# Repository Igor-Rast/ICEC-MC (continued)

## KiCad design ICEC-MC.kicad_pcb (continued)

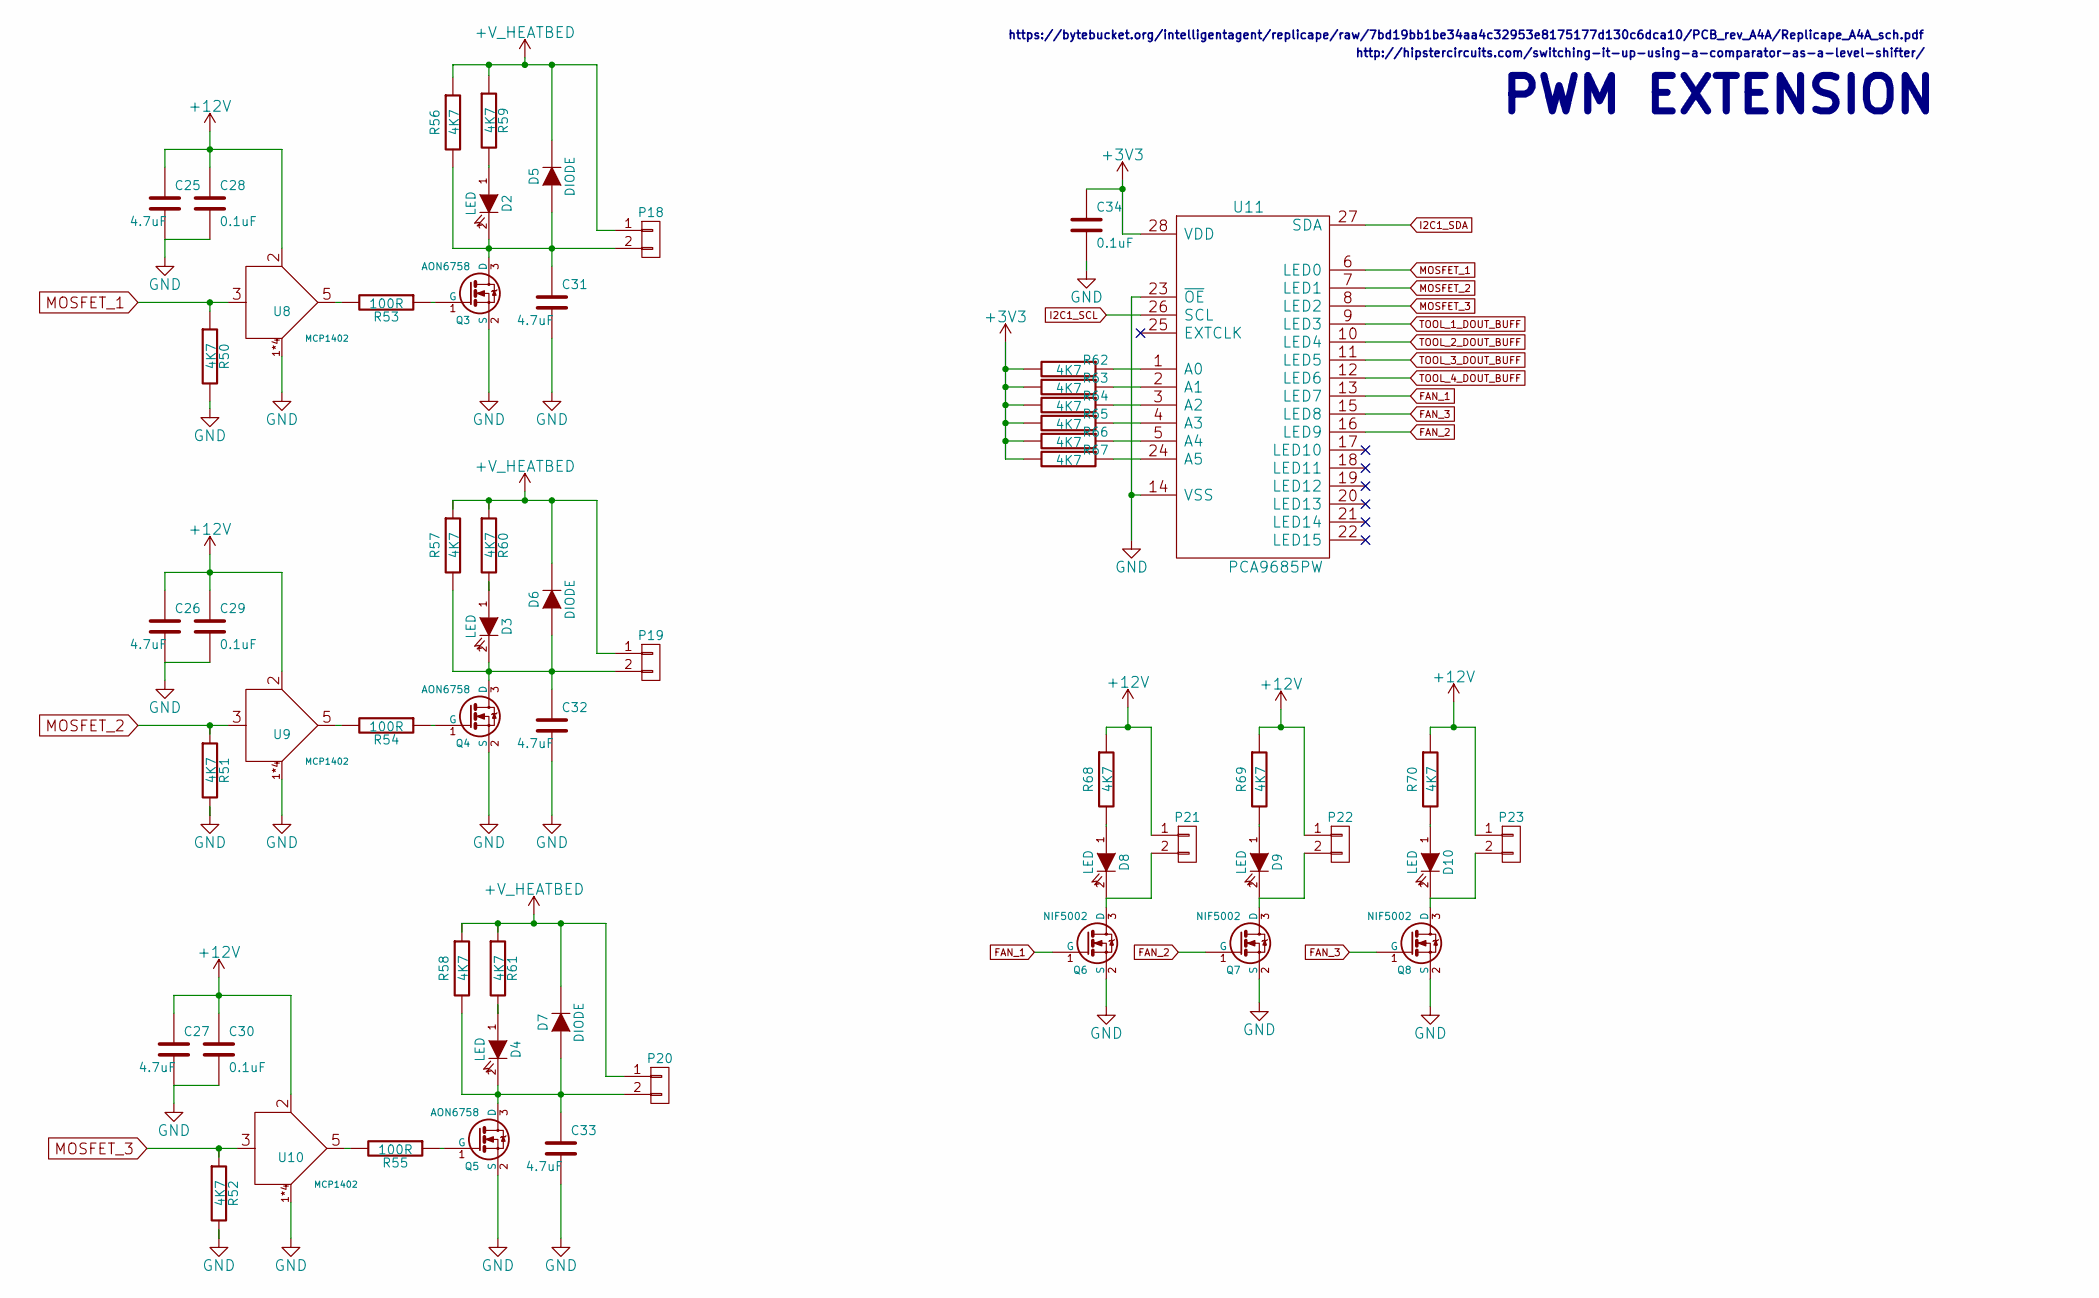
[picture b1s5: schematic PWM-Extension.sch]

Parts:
C25, C26, C27, C31, C32, C33: 4.7uF; C_0805_HandSoldering
C28, C29, C30, C34: 0.1uF; C_0805_HandSoldering
D2, D3, D4, D9, D10: LED; LED-0603
D5, D6, D7: DIODE
D8: LED; LED-0603; DigiKey 475-2816-1-ND
P18, P19, P20, P21, P22, P23: CONN_01X02; Socket_Strip_Straight_1x02
Q3, Q4, Q5: AON6758
Q6, Q7, Q8: NIF5002
R50, R51, R52, R56, R57, R58, R59, R60, R61, R62, R63, R64, R65, R66, R67, R68, R69, R70: 4K7; R_0805_HandSoldering
R53, R54, R55: 100R; R_0805_HandSoldering
U8, U9, U10: MCP1402
U11: PCA9685PW; TSSOP-28_4.4x9.7mm_Pitch0.65mm

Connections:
+3V3: C34.1, R62.2, R63.2, R64.2, R65.2, R66.2, R67.2, U11.28 (VDD); also elsewhere on the board
FAN_1: Q6.1 (G), U11.13 (LED7)
FAN_2: Q7.1 (G), U11.16 (LED9)
FAN_3: Q8.1 (G), U11.15 (LED8)
I2C1_SCL: U11.26 (SCL); also elsewhere on the board
I2C1_SDA: U11.27 (SDA); also elsewhere on the board
MOSFET_1: R50.1, U8.3, U11.6 (LED0)
MOSFET_2: R51.1, U9.3, U11.7 (LED1)
MOSFET_3: R52.1, U10.3, U11.8 (LED2)
unnamed: C31.1, D2.2 (K), D5.1 (A), P18.2, Q3.3 (D), R56.2
unnamed: C32.1, D3.2 (K), D6.1 (A), P19.2, Q4.3 (D), R57.2
unnamed: C33.1, D4.2 (K), D7.1 (A), P20.2, Q5.3 (D), R58.2
unnamed: D2.1 (A), R59.2
unnamed: D3.1 (A), R60.2
unnamed: D4.1 (A), R61.2
unnamed: D8.1 (A), R68.2
unnamed: D8.2 (K), P21.2, Q6.3 (D)
unnamed: D9.1 (A), R69.2
unnamed: D9.2 (K), P22.2, Q7.3 (D)
unnamed: D10.1 (A), R70.2
unnamed: D10.2 (K), P23.2, Q8.3 (D)
unnamed: Q3.1 (G), R53.1
unnamed: Q4.1 (G), R54.1
unnamed: Q5.1 (G), R55.1
unnamed: R53.2, U8.5
unnamed: R54.2, U9.5
unnamed: R55.2, U10.5
unnamed: R62.1, U11.1 (A0)
unnamed: R63.1, U11.2 (A1)
unnamed: R64.1, U11.3 (A2)
unnamed: R65.1, U11.4 (A3)
unnamed: R66.1, U11.5 (A4)
unnamed: R67.1, U11.24 (A5)
TOOL_1_DOUT_BUFF: U11.9 (LED3); also elsewhere on the board
TOOL_2_DOUT_BUFF: U11.10 (LED4); also elsewhere on the board
TOOL_3_DOUT_BUFF: U11.11 (LED5); also elsewhere on the board
TOOL_4_DOUT_BUFF: U11.12 (LED6); also elsewhere on the board

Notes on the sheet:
PWM EXTENSION
http://hipstercircuits.com/switching-it-up-using-a-comparator-as-a-level-shifter/
https://bytebucket.org/intelligentagent/replicape/raw/7bd19bb1be34aa4c32953e8175177d130c6dca10/PCB_rev_A4A/Replicape_A4A_sch.pdf

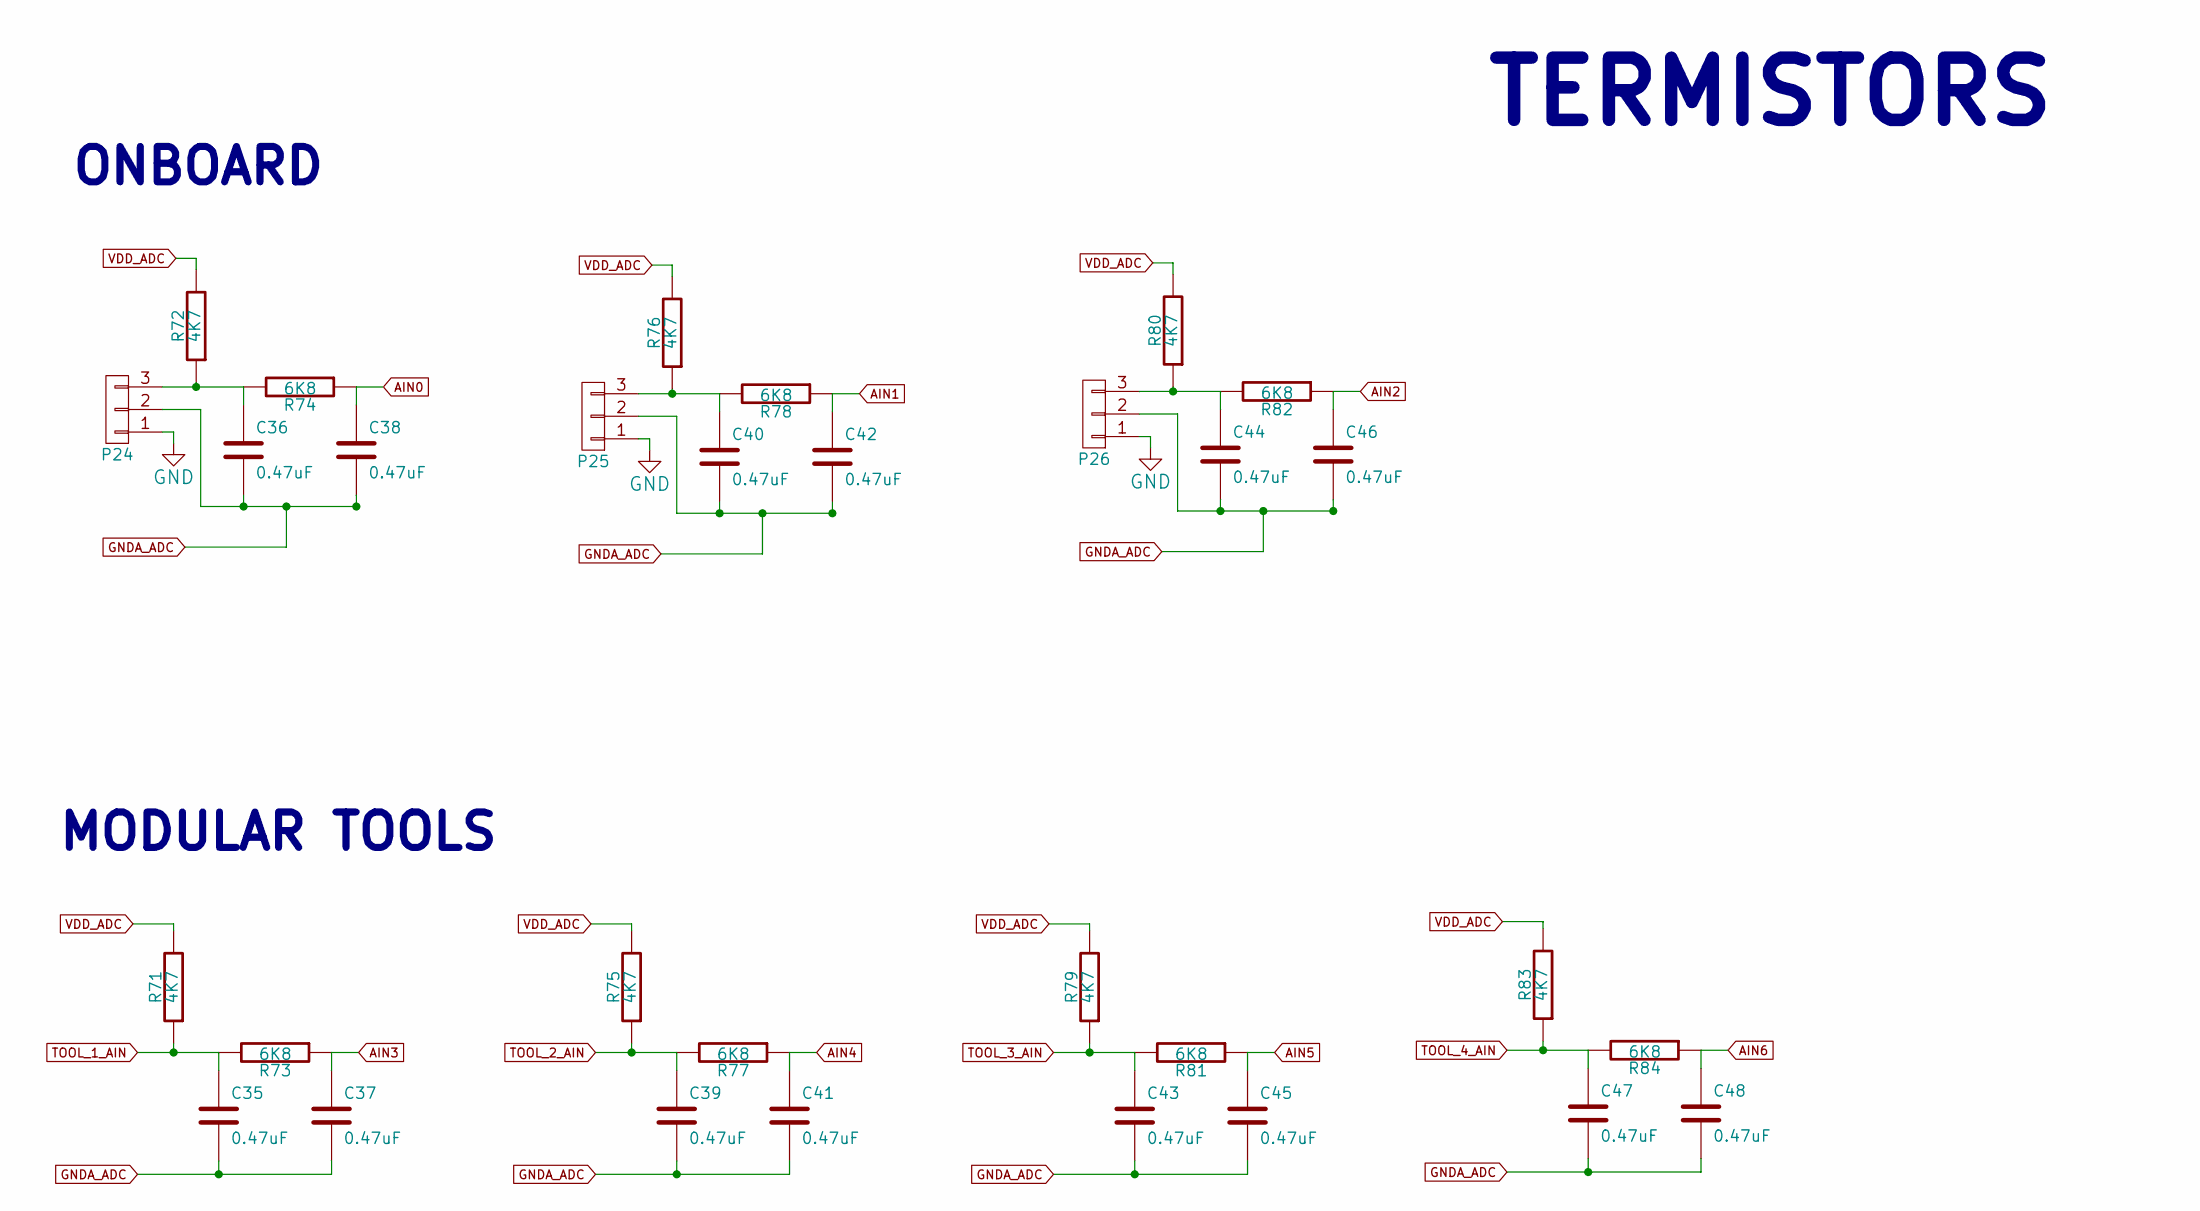
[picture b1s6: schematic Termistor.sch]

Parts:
C35, C36, C37, C38, C39, C40, C41, C42, C43, C44, C45, C46, C47, C48: 0.47uF; C_0805_HandSoldering
P24, P25, P26: CONN_01X03; Socket_Strip_Straight_1x03
R71, R72, R75, R76, R79, R80, R83: 4K7; R_0805_HandSoldering
R73, R74, R77, R78, R81, R82, R84: 6K8; R_0805_HandSoldering

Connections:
AIN0: C38.1, R74.1; also elsewhere on the board
AIN1: C42.1, R78.1; also elsewhere on the board
AIN2: C46.1, R82.1; also elsewhere on the board
AIN3: C37.1, R73.1; also elsewhere on the board
AIN4: C41.1, R77.1; also elsewhere on the board
AIN5: C45.1, R81.1; also elsewhere on the board
AIN6: C48.1, R84.1; also elsewhere on the board
GNDA_ADC: C35.2, C36.2, C37.2, C38.2, C39.2, C40.2, C41.2, C42.2, C43.2, C44.2, C45.2, C46.2, C47.2, C48.2, P24.2, P25.2, P26.2; also elsewhere on the board
unnamed: C36.1, P24.3, R72.1, R74.2
unnamed: C40.1, P25.3, R76.1, R78.2
unnamed: C44.1, P26.3, R80.1, R82.2
TOOL_1_AIN: C35.1, R71.1, R73.2; also elsewhere on the board
TOOL_2_AIN: C39.1, R75.1, R77.2; also elsewhere on the board
TOOL_3_AIN: C43.1, R79.1, R81.2; also elsewhere on the board
TOOL_4_AIN: C47.1, R83.1, R84.2; also elsewhere on the board
VDD_ADC: R71.2, R72.2, R75.2, R76.2, R79.2, R80.2, R83.2; also elsewhere on the board

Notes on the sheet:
TERMISTORS
ONBOARD
MODULAR TOOLS

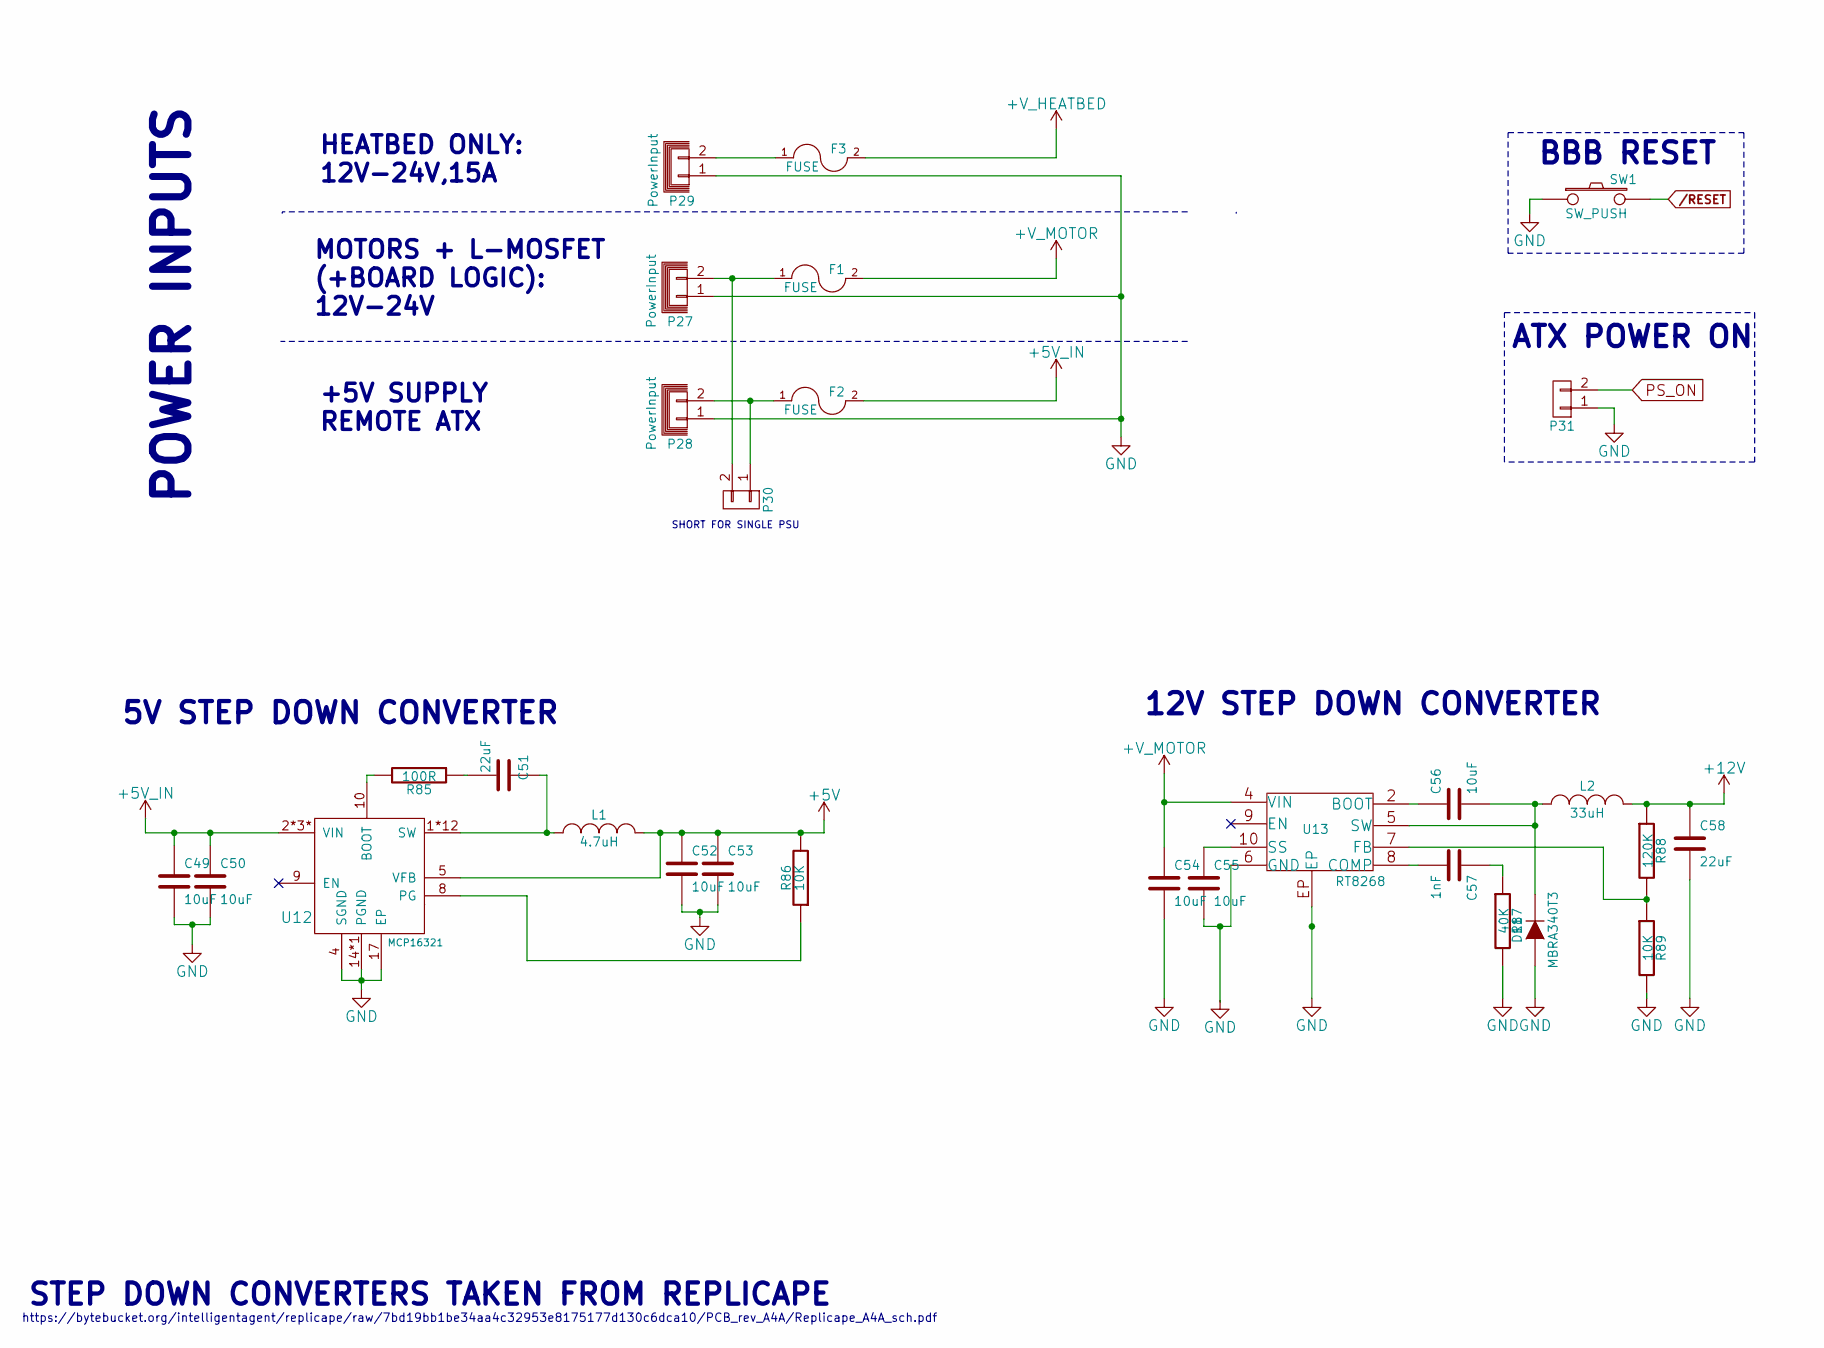
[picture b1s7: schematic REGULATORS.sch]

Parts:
C49, C50, C52, C53, C54, C55, C56: 10uF; C_0805_HandSoldering
C51, C58: 22uF; C_0805_HandSoldering
C57: 1nF; C_0805_HandSoldering
D11: MBRA340T3
F1, F2, F3: FUSE
L1: 4.7uH
L2: 33uH
P27, P28, P29: PowerInput; Socket_Strip_Straight_1x02
P30, P31: CONN_01X02; Socket_Strip_Straight_1x02
R85: 100R; R_0805_HandSoldering
R86, R89: 10K; R_0805_HandSoldering
R87: 40K; R_0805_HandSoldering
R88: 120K; R_0805_HandSoldering
SW1: SW_PUSH
U12: MCP16321
U13: RT8268

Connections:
+5V: C52.1, C53.1, L1.2, R86.2, U12.5 (VFB); also elsewhere on the board
+5VD: C49.1, C50.1, F2.2, U12.2*3* (VIN)
+V_MOTOR: C54.1, F1.2, U13.4 (VIN); also elsewhere on the board
unnamed: C51.1, L1.1, U12.1*12 (SW)
unnamed: C51.2, R85.1
unnamed: C55.1, U13.10 (SS)
unnamed: C56.1, U13.2 (BOOT)
unnamed: C56.2, D11.2 (K), L2.1, U13.5 (SW)
unnamed: C57.1, R87.1
unnamed: C57.2, U13.8 (COMP)
unnamed: F1.1, P27.2, P30.2
unnamed: F2.1, P28.2, P30.1
unnamed: F3.1, P29.2
unnamed: R85.2, U12.10 (BOOT)
unnamed: R86.1, U12.8 (PG)
unnamed: R88.2, R89.1, U13.7 (FB)
PS_ON: P31.2; also elsewhere on the board

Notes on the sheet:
ATX POWER ON
SHORT FOR SINGLE PSU
HEATBED ONLY: 12V-24V,15A
MOTORS + L-MOSFET (+BOARD LOGIC): 12V-24V
+5V SUPPLY REMOTE ATX
POWER INPUTS
BBB RESET
5V STEP DOWN CONVERTER
https://bytebucket.org/intelligentagent/replicape/raw/7bd19bb1be34aa4c32953e8175177d130c6dca10/PCB_rev_A4A/Replicape_A4A_sch.pdf
STEP DOWN CONVERTERS TAKEN FROM REPLICAPE
12V STEP DOWN CONVERTER

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
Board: 2 copper layers, 202 parts (2 on the bottom side), 186 nets, no tracks yet.

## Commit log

2015-02-16 first release
2015-02-18 Add Some Info about project
